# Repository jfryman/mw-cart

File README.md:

# mw-cart
MegaWiFi Cartridge

> **This is the MegaWiFi Rev.C fork** of [doragasu/mw-cart](https://gitlab.com/doragasu/mw-cart).
> Everything below the "Rev.C" section is doragasu's original README.

## Rev.C (this fork)

**What changed (2026-10-06, jfryman):** the NXP **SC16C550BIBS** UART (U7) is out of stock
everywhere, so Rev.C replaces it with the pin-compatible **TI TL16C550DRHB** (VQFN-32, RHB):

| | Rev.B (upstream) | Rev.C |
|---|---|---|
| U7 UART | NXP SC16C550BIBS | TI TL16C550DRHB (LCSC C2653239) |
| Y1 crystal | 24 MHz | **20 MHz** (C252261) + R18 1 MΩ bias resistor |
| Cart ↔ ESP32 link | 1.5 Mbaud | **1.25 Mbaud** |
| RI pin | NC | tied to VCC |

The TI part is rated to 20 MHz at 3.3 V, so the UART link runs at 1.25 Mbaud. **Rev.C is not
compatible with existing MegaWiFi ROMs or firmware**: ROMs need `UART_CLK` 20 MHz in their
`16c550.h`, and the ESP32 needs the Rev.C firmware from
[jfryman/mw-fw-rtos](https://github.com/jfryman/mw-fw-rtos/releases). Title blocks and silkscreen
are marked Rev.C.

**Status:** 10 boards assembled by JLCPCB (2026-10). The first board passes the full bring-up
suite at 1.25 Mbaud, including the flat 8 MiB ROM map with a Mega-CD and 32X attached.

**In this repo, beyond upstream:**
- `bringup-rom/`: a standalone 68000 test ROM for new boards (UART, crystal, ESP32 link,
  flash address lines, the 8 MiB map), plus a MAME simulation and FlashKit MD helper scripts.
- `tools/`: kicad-cli build wrapper and the KiCad s-expression helpers used for the U7 swap.
  `tools/fetch-ext.sh` fetches the Espressif 3D models.
- `lode/`: design notes, decisions and bench results.

**Downloads** ([releases](https://github.com/jfryman/mw-cart/releases)): JLCPCB Gerber zip,
BOM and CPL, schematic and fab PDFs, and the bring-up ROM. Upstream's own Rev.B outputs are on
[GitLab](https://gitlab.com/doragasu/mw-cart). Their BOM lists the unobtainable SC16C550BIBS.

---

This is the cartridge for the MegaWiFi project. It consists of a cartridge for the SEGA Genesis/Megadrive console, along with a WiFi interface, allowing brave programmers to implement games with online gaming, leaderboards, evil DLCs, etc.

This project was initially created for 1985alternativo, and to this day, as far as I know, only 1985 WorldCup game has used it to implement online play. Will you give it a try?

Have a look to the [github project page](https://gitlab.com/doragasu/mw) for more information.

## Cartridge specs

The current cartridge is based on an ESP32-C3 WiFi microcontroller, that has a good specs/price tradeoff. But bear in mind that if needed, it would be easy swapping it for other more powerful ESP32 chip, like for example the ESP32-S3. The current specs are:

* Up to 64 megabits (8 MiB) of flat ROM (no mapper needed!).
* Fast ESP32 to m68k UART bridge (1.5 Mbps baud rate with hardware flow control; 1.25 Mbps on Rev.C).
* 32-bit RISC-V CPU running at 160 MHz. Can be upgraded to dual core up to 240 MHz if needed.
* Additional 16 megabits (2 MiB) available of readable/writable memory (managed by the ESP32 and accessed through the UART bridge, could be upgraded to up to 14 MiB if needed!).
* 400 KiB of SRAM managed by the ESP32.
* 802.11bgn Wi-Fi (2.4 GHz band) with WPA3 support.
* Bluetooth Low Energy (BLE) support.
* USB port for ESP32 programming and debugging. Can be upgraded to work as general purpose USB host/device port.
* Connection to the cart audio input, so the chip could be used to produce additional sound (though there is no software support for this yet).

**Note**: The cartridge slashes the the usual 32 megabits maximum of ROM space by implementing a hack: it unmaps the MegaCD and uses its address space. This has the drawback that you cannot access the MegaCD when the hack is enabled. If you need to access the MegaCD, the hack can be disabled, but then the cart is limited to the usual 32 megabits of ROM.

## License
mw-cart is licensed under the [CERN OHL 1.2](http://www.ohwr.org/licenses/cern-ohl/v1.2) license. You are free to study, distribute and make modifications to the Documentation, under the aforementioned license terms.

## About CAD files
Electronic CAD design files are for KiCAD Open Source electronics design suite. Please install latest version along with KiCAD libraries to open the project. When opening schematic, KiCAD will most likely complain about missing library "doragasu". Despite this warning, the schematic should load nicely (using the cached libraries). To avoid this message, install [the missing library](https://github.com/doragasu/doragasu-kicad-lib) and make sure to configure it in the schematic editor.

## Board fabrication

You can go to [the package registry](https://gitlab.com/doragasu/mw-cart/-/packages) to download artifact packages with the fabrication files, including Gerbers, bill of materials, drawings, CPL file, etc. To get the PCB made, you sould have some knowledge about PCB manufacturing, but I will try to give some indications about how to get the boards made and assembled by JLCPCB.

### Manufacturing process example: JLCPCB

[JLCPCB](https://jlcpcb.com/) is a widely known Chinese PCB manufacturer, that can do PCB fabrication and assembly, including component procurement. They are fairly cheap for PCB prototypes and quality is pretty good for boards not having difficult components (such as BGAs with very fine pitch). One of the things that make them have quite competitive pricing, is that **they will only assemble components they have stocked**. Luckily they source components from [LCSC](https://www.lcsc.com/) (one of the biggest Chinese suppliers) and have a very wide catalog of components. But even with this wide catalog it is not uncommon that one or more of the components for your board are not available. In this case, they allow you to purchase the components through their platform, and once they receive them, they can be selected for assembly on your boards.

So roughly speaking, the procedure to order assembled PCBs on JLCPCB is as follows:

1. Get a quotation for PCB manufacturing and assembly.
2. If all components required for assembly are available, awesome, make the order and you have finished. Otherwise, purchase the components using their *Parts Manager*. Once purchased, stocked components usually take 2 or 3 weeks to be received by JLCPCB, and they will notify you via email.
3. Repeat step one, components you purchased through *Parts Manager* will be available for assembly on your boards.

Getting into the details, the procedure is:

1. Download the [PCB artifact package](https://gitlab.com/doragasu/mw-cart/-/packages) from the package registry.
2. Extract the package and locate the `Fab/Manufacturers/mega-wifi-JLCPCB.zip` file, that contains the Gerber files, the `Fab/Manufacturers/JLCPCB/mega-wifi_bom_jlc.csv` that has the BoM (Bill of Materials) and the `Fab/Manufacturers/JLCPCB/mega-wifi_cpl_jlc.csv` that has the CPL (Component Placement/Centroid) file. We will have to upload these files later.
3. Go to [JLCPCB](https://jlcpcb.com/) and log into your account. Then click *Order now* on the top right of the page.
4. Click *Add gerber file* and upload the `mega-wifi-JLCPCB.zip` file we located in step 2. When the files are processed, many board parameters will be populated. Most of the default values will be OK, but some changes are recommended. I will mark with an asterisk (\*) the parameters that should be changed from defaults, and will omit some parameters that should be clear enough (like PCB quantity, color, or dimensions that will be automatically obtained from Gerber files):

* Base material: FR-4
* Layers: 2
* PCB Thickness: 1.6
* Surface Finish: ENIG (\*)
* Outer Copper Weight: 1 oz
* Via Covering: Tented
* Min via hole size/diameter: 0.3mm
* Board Outline Tolerance: +- 0.2mm(Regular)
* Gold Fingers: Yes (\*)
* 30°finger chamfered: Yes (\*)
* Castellated Holes: No
* Edge Plating: No

5. If you want assembly, enable the *PCB Assembly* slider. All the default assembly parameters should be OK:

* PCBA Type: Standard
* Assembly Side: Top Side
* Edge Rails/Fiducials: Added by JLCPCB
* Parts Selection: By Customer

Advanced options defaults should also be OK.

6. Click "Next", you will be asked for confirmation about the side that will be assembled and the assembly quantity. Again, click "Next". Then you will be prompted for the BOM and CPL files. Upload the `mega-wifi_bom_jlc.csv` and `mega-wifi_cpl_jlc.csv` files we located in step 2. Then click "Process BOM & CPL".
7. You will be presented the table of components that will be assembled. If you are lucky, everything will be stocked so you can click "Next" and jump to step 12. Otherwise take note of the non stocked components (and I would also recommend taking note of stocked components having low stock) and continue to step 8.
8. Open the "Parts Manager" and the "Order Parts" on the left column.
9. Search for the non stocked parts from step 7. I would recommend searching first on the "JLCPCB Parts" section (that is usually cheaper and faster), but most likely you will have to search in the "Global Sourcing Parts". I would recommend only purchasing components in stock, because orders with components having a Lead Time, in my experience sometimes get heavily delayed or even cancelled.
10. Complete the components order, and wait till they are received by JLCPCB (they will notify by email). For stocked components, this should take 2 or 3 weeks max.
11. Repeat steps 1 to 7. Now you should be able to select your purchased components for the assembly.
12. You will be presented a component placement preview. It is a common issue that all components have a wrong offset from the board origin, and some can be wrongly rotated. Do not worry, this is normal and will be later corrected by the DFM analysis. Just click "Next".
13. You can now review the order, place it to the cart and proceed to checkout. Done! Just have to wait for the boards to arrive to your door. Be warned though that depending on your country and the shipping method, you might have to fill additional paperwork and pay import customs.

Enjoy!

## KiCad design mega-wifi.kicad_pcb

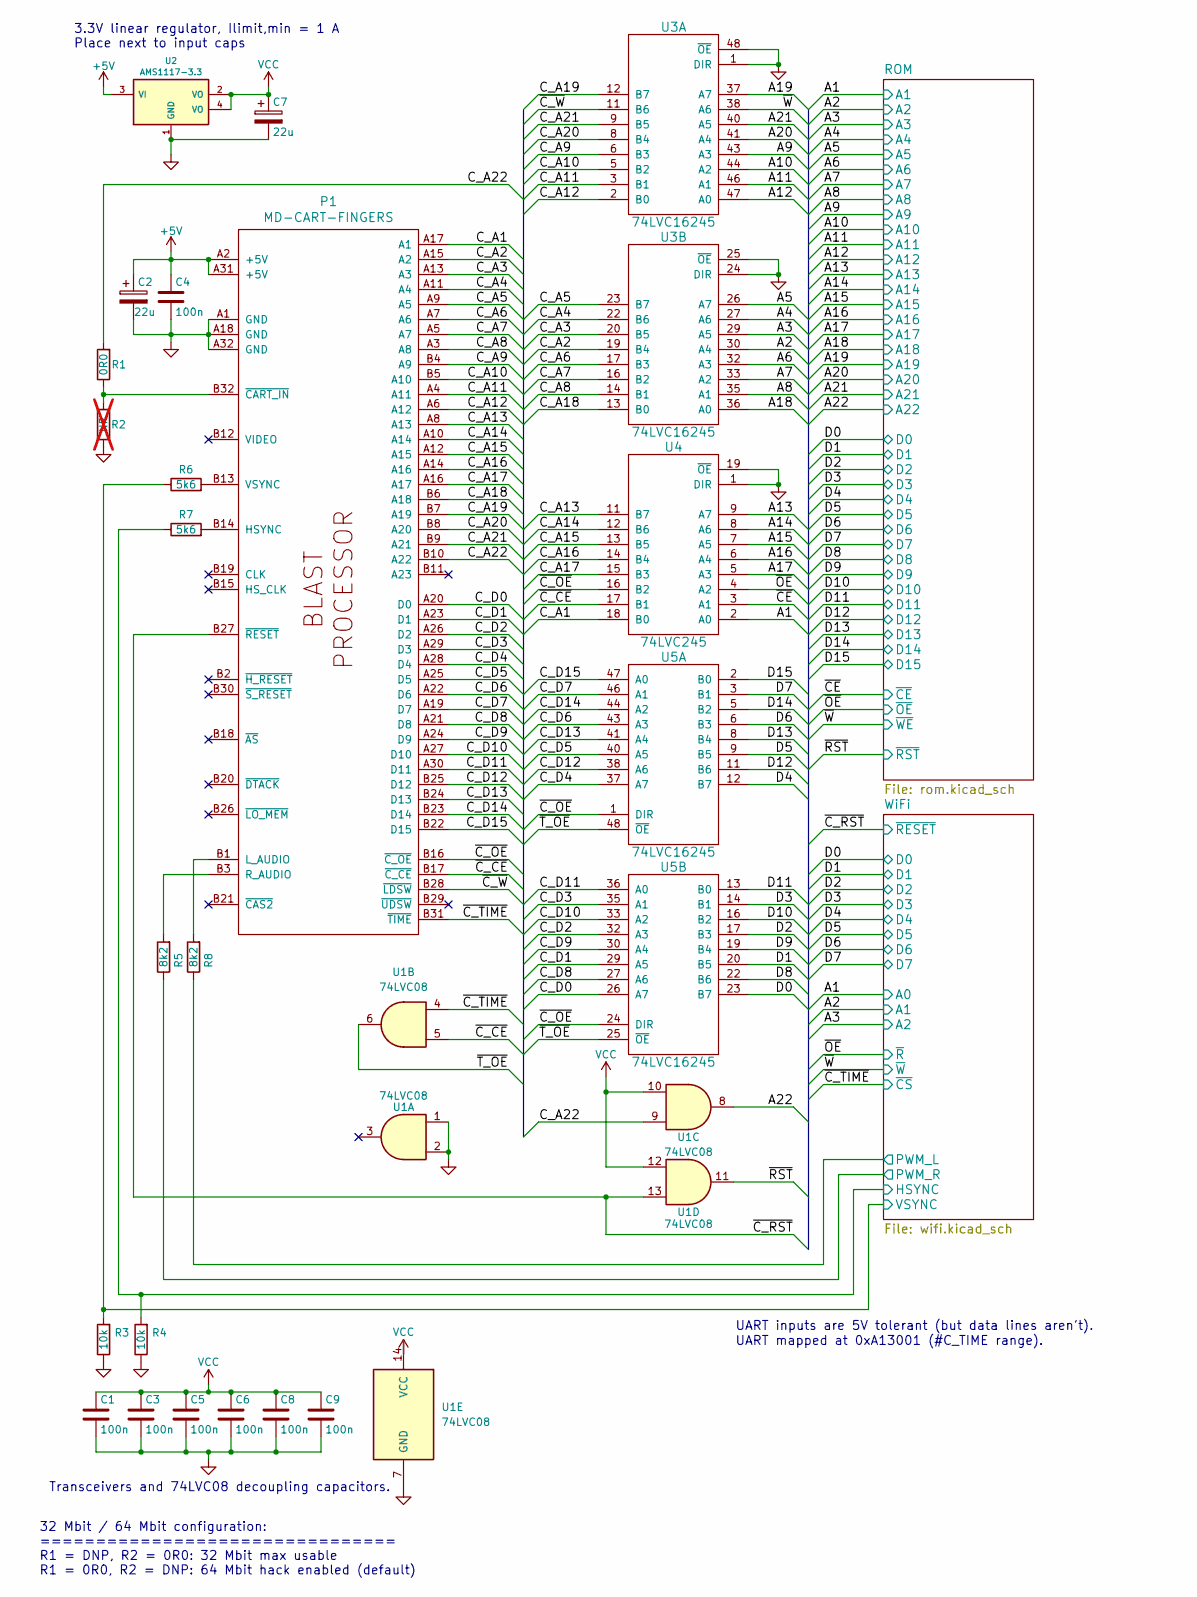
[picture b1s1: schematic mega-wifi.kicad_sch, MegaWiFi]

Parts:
C1, C3, C4, C5, C6, C8, C9: 100n; C_0603_1608Metric; LCSC# C14663
C2, C7: 22u; C_1206_3216Metric; LCSC# C12891
P1: MD-CART-FINGERS
R1: 0R0; R_0603_1608Metric; LCSC# C21189
R2: NP; R_0603_1608Metric; not fitted
R3, R4: 10k; R_0603_1608Metric; LCSC# C25804
R5, R8: 8k2; R_0603_1608Metric; LCSC# C25981
R6, R7: 5k6; R_0603_1608Metric; LCSC# C23189
U1: 74LVC08; TSSOP-14_4.4x5mm_P0.65mm; LCSC# C6053
U2: AMS1117-3.3; SOT-223; LCSC# C6186
U3, U5: 74LVC16245; TSSOP-48_6.1x12.5mm_P0.5mm; LCSC# C7824
U4: 74LVC245; TSSOP-20_4.4x6.5mm_P0.65mm; LCSC# C7848

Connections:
+5V: C2.1, C4.1, P1.A2 (+5V), P1.A31 (+5V), U2.3 (VI); also elsewhere on the board
/A1: U4.2 (A0); also elsewhere on the board
/A2: U3.30 (A4); also elsewhere on the board
/A3: U3.29 (A5); also elsewhere on the board
/A4: U3.27 (A6); also elsewhere on the board
/A5: U3.26 (A7); also elsewhere on the board
/A6: U3.32 (A3); also elsewhere on the board
/A7: U3.33 (A2); also elsewhere on the board
/A8: U3.35 (A1); also elsewhere on the board
/A9: U3.43 (A3); also elsewhere on the board
/A10: U3.44 (A2); also elsewhere on the board
/A11: U3.46 (A1); also elsewhere on the board
/A12: U3.47 (A0); also elsewhere on the board
/A13: U4.9 (A7); also elsewhere on the board
/A14: U4.8 (A6); also elsewhere on the board
/A15: U4.7 (A5); also elsewhere on the board
/A16: U4.6 (A4); also elsewhere on the board
/A17: U4.5 (A3); also elsewhere on the board
/A18: U3.36 (A0); also elsewhere on the board
/A19: U3.37 (A7); also elsewhere on the board
/A20: U3.41 (A4); also elsewhere on the board
/A21: U3.40 (A5); also elsewhere on the board
/A22: U1.8; also elsewhere on the board
/C_A1: P1.A17 (A1), U4.18 (B0)
/C_A2: P1.A15 (A2), U3.19 (B4)
/C_A3: P1.A13 (A3), U3.20 (B5)
/C_A4: P1.A11 (A4), U3.22 (B6)
/C_A5: P1.A9 (A5), U3.23 (B7)
/C_A6: P1.A7 (A6), U3.17 (B3)
/C_A7: P1.A5 (A7), U3.16 (B2)
/C_A8: P1.A3 (A8), U3.14 (B1)
/C_A9: P1.B4 (A9), U3.6 (B3)
/C_A10: P1.B5 (A10), U3.5 (B2)
/C_A11: P1.A4 (A11), U3.3 (B1)
/C_A12: P1.A6 (A12), U3.2 (B0)
/C_A13: P1.A8 (A13), U4.11 (B7)
/C_A14: P1.A10 (A14), U4.12 (B6)
/C_A15: P1.A12 (A15), U4.13 (B5)
/C_A16: P1.A14 (A16), U4.14 (B4)
/C_A17: P1.A16 (A17), U4.15 (B3)
/C_A18: P1.B6 (A18), U3.13 (B0)
/C_A19: P1.B7 (A19), U3.12 (B7)
/C_A20: P1.B8 (A20), U3.8 (B4)
/C_A21: P1.B9 (A21), U3.9 (B5)
/C_A22: P1.B10 (A22), R1.2, U1.9
/C_D0: P1.A20 (D0), U5.26 (A7)
/C_D1: P1.A23 (D1), U5.29 (A5)
/C_D2: P1.A26 (D2), U5.32 (A3)
/C_D3: P1.A29 (D3), U5.35 (A1)
/C_D4: P1.A28 (D4), U5.37 (A7)
/C_D5: P1.A25 (D5), U5.40 (A5)
/C_D6: P1.A22 (D6), U5.43 (A3)
/C_D7: P1.A19 (D7), U5.46 (A1)
/C_D8: P1.A21 (D8), U5.27 (A6)
/C_D9: P1.A24 (D9), U5.30 (A4)
/C_D10: P1.A27 (D10), U5.33 (A2)
/C_D11: P1.A30 (D11), U5.36 (A0)
/C_D12: P1.B25 (D12), U5.38 (A6)
/C_D13: P1.B24 (D13), U5.41 (A4)
/C_D14: P1.B23 (D14), U5.44 (A2)
/C_D15: P1.B22 (D15), U5.47 (A0)
/D0: U5.23 (B7); also elsewhere on the board
/D1: U5.20 (B5); also elsewhere on the board
/D2: U5.17 (B3); also elsewhere on the board
/D3: U5.14 (B1); also elsewhere on the board
/D4: U5.12 (B7); also elsewhere on the board
/D5: U5.9 (B5); also elsewhere on the board
/D6: U5.6 (B3); also elsewhere on the board
/D7: U5.3 (B1); also elsewhere on the board
/D8: U5.22 (B6); also elsewhere on the board
/D9: U5.19 (B4); also elsewhere on the board
/D10: U5.16 (B2); also elsewhere on the board
/D11: U5.13 (B0); also elsewhere on the board
/D12: U5.11 (B6); also elsewhere on the board
/D13: U5.8 (B4); also elsewhere on the board
/D14: U5.5 (B2); also elsewhere on the board
/D15: U5.2 (B0); also elsewhere on the board
/WiFi/HSYNC: R4.2, R7.1; also elsewhere on the board
/WiFi/PWM_L: R8.1; also elsewhere on the board
/WiFi/PWM_R: R5.1; also elsewhere on the board
/WiFi/VSYNC: R3.2, R6.1; also elsewhere on the board
/~CE: U4.3 (A1); also elsewhere on the board
/~C_CE: P1.B17 (~C_CE), U1.5, U4.17 (B1)
/~C_OE: P1.B16 (~C_OE), U4.16 (B2), U5.1 (DIR), U5.24 (DIR)
/~C_RST: P1.B27 (~RESET), U1.13; also elsewhere on the board
/~C_TIME: P1.B31 (~TIME), U1.4; also elsewhere on the board
/~C_W: P1.B28 (~LDSW), U3.11 (B6)
/~OE: U4.4 (A2); also elsewhere on the board
/~RST: U1.11; also elsewhere on the board
/~T_OE: U1.6, U5.25 (~OE), U5.48 (~OE)
/~W: U3.38 (A6); also elsewhere on the board
GND: C1.2, C2.2, C3.2, C4.2, C5.2, C6.2, C7.2, C8.2, C9.2, P1.A1 (GND), P1.A18 (GND), P1.A32 (GND), R2.1, R3.1, R4.1, U1.1, U1.2, U1.7 (GND), U2.1 (GND), U3.1 (DIR), U3.4 (GND), U3.10 (GND), U3.15 (GND), U3.21 (GND), U3.24 (DIR), U3.25 (~OE), U3.28 (GND), U3.34 (GND), U3.39 (GND), U3.45 (GND), U3.48 (~OE), U4.1 (DIR), U4.10 (GND), U4.19 (~OE), U5.4 (GND), U5.10 (GND), U5.15 (GND), U5.21 (GND), U5.28 (GND), U5.34 (GND), U5.39 (GND), U5.45 (GND); also elsewhere on the board
unnamed: P1.B14 (HSYNC), R7.2
unnamed: P1.B1 (L_AUDIO), R8.2
unnamed: P1.B3 (R_AUDIO), R5.2
unnamed: P1.B13 (VSYNC), R6.2
unnamed: P1.B32 (~CART_IN), R1.1, R2.2
VCC: C1.1, C3.1, C5.1, C6.1, C7.1, C8.1, C9.1, U1.10, U1.12, U1.14 (VCC), U2.2 (VO), U2.4 (VO), U3.7 (VCC), U3.18 (VCC), U3.31 (VCC), U3.42 (VCC), U4.20 (VCC), U5.7 (VCC), U5.18 (VCC), U5.31 (VCC), U5.42 (VCC); also elsewhere on the board

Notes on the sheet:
UART mapped at 0xA13001 (#C_TIME range).
32 Mbit / 64 Mbit configuration: ================================ R1 = DNP, R2 = 0R0: 32 Mbit max usable R1 = 0R0, R2 = DNP: 64 Mbit hack enabled (default)
Transceivers and 74LVC08 decoupling capacitors.
UART inputs are 5V tolerant (but data lines aren't).
3.3V linear regulator, Ilimit,min = 1 A Place next to input caps

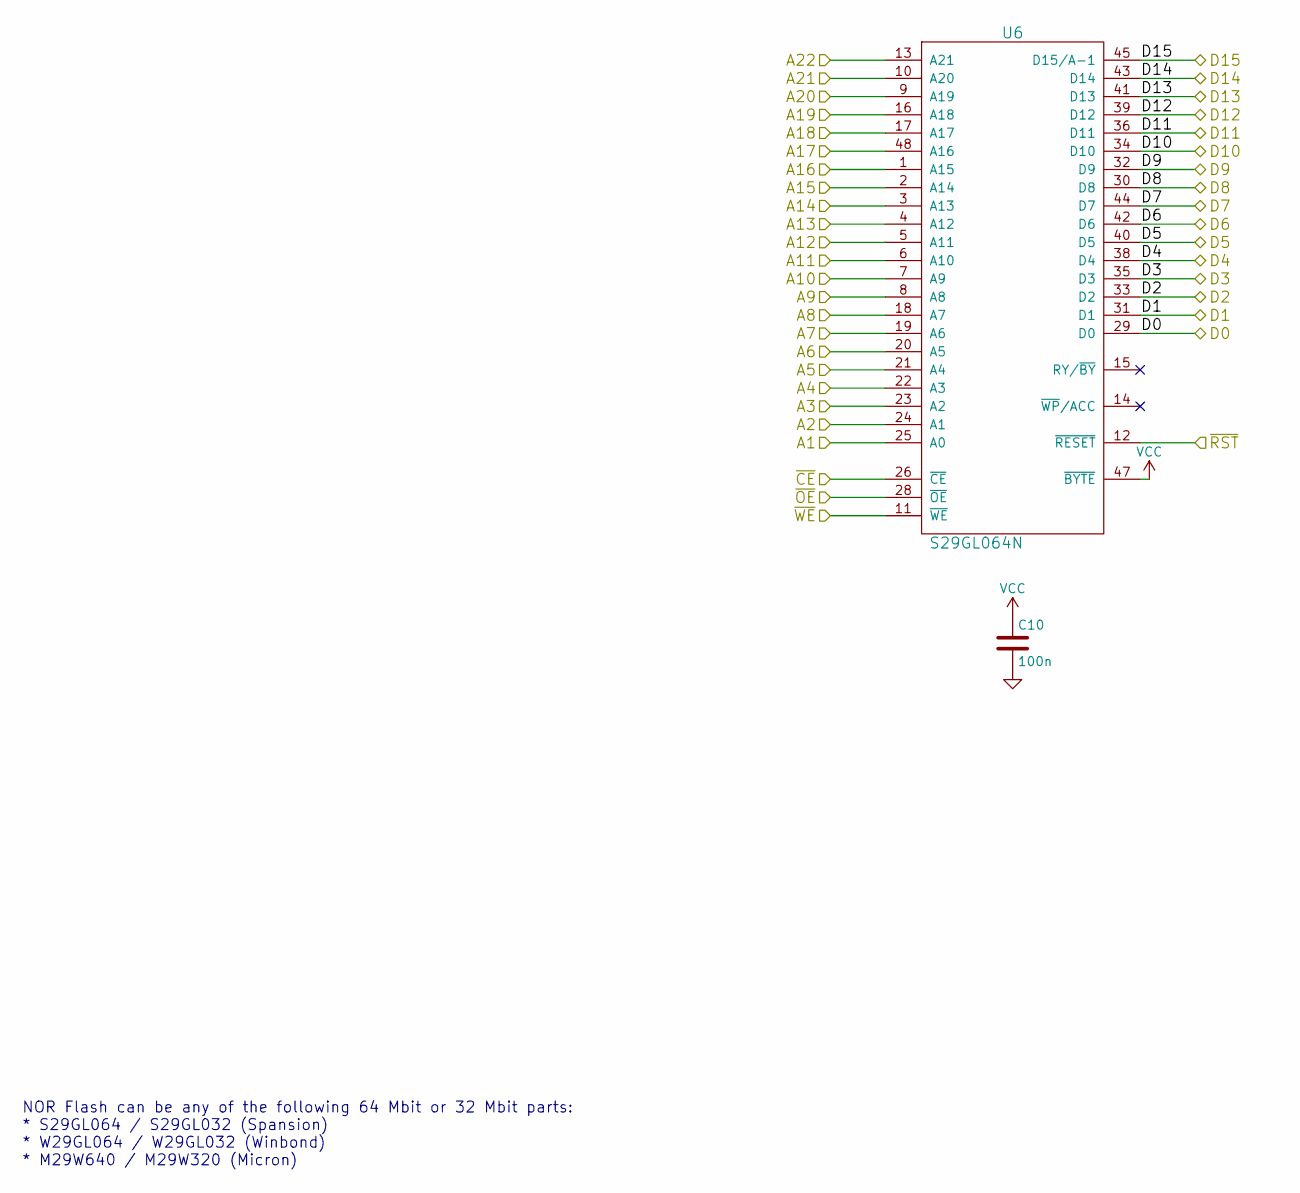
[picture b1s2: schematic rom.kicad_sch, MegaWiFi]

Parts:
C10: 100n; C_0603_1608Metric; LCSC# C14663
U6: S29GL064N; TSOP-I-48_18.4x12mm_P0.5mm; LCSC# C117907

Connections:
/A1: U6.25 (A0); also elsewhere on the board
/A2: U6.24 (A1); also elsewhere on the board
/A3: U6.23 (A2); also elsewhere on the board
/A4: U6.22 (A3); also elsewhere on the board
/A5: U6.21 (A4); also elsewhere on the board
/A6: U6.20 (A5); also elsewhere on the board
/A7: U6.19 (A6); also elsewhere on the board
/A8: U6.18 (A7); also elsewhere on the board
/A9: U6.8 (A8); also elsewhere on the board
/A10: U6.7 (A9); also elsewhere on the board
/A11: U6.6 (A10); also elsewhere on the board
/A12: U6.5 (A11); also elsewhere on the board
/A13: U6.4 (A12); also elsewhere on the board
/A14: U6.3 (A13); also elsewhere on the board
/A15: U6.2 (A14); also elsewhere on the board
/A16: U6.1 (A15); also elsewhere on the board
/A17: U6.48 (A16); also elsewhere on the board
/A18: U6.17 (A17); also elsewhere on the board
/A19: U6.16 (A18); also elsewhere on the board
/A20: U6.9 (A19); also elsewhere on the board
/A21: U6.10 (A20); also elsewhere on the board
/A22: U6.13 (A21); also elsewhere on the board
/D0: U6.29 (D0); also elsewhere on the board
/D1: U6.31 (D1); also elsewhere on the board
/D2: U6.33 (D2); also elsewhere on the board
/D3: U6.35 (D3); also elsewhere on the board
/D4: U6.38 (D4); also elsewhere on the board
/D5: U6.40 (D5); also elsewhere on the board
/D6: U6.42 (D6); also elsewhere on the board
/D7: U6.44 (D7); also elsewhere on the board
/D8: U6.30 (D8); also elsewhere on the board
/D9: U6.32 (D9); also elsewhere on the board
/D10: U6.34 (D10); also elsewhere on the board
/D11: U6.36 (D11); also elsewhere on the board
/D12: U6.39 (D12); also elsewhere on the board
/D13: U6.41 (D13); also elsewhere on the board
/D14: U6.43 (D14); also elsewhere on the board
/D15: U6.45 (D15/A-1); also elsewhere on the board
/~CE: U6.26 (~CE); also elsewhere on the board
/~OE: U6.28 (~OE); also elsewhere on the board
/~RST: U6.12 (~RESET); also elsewhere on the board
/~W: U6.11 (~WE); also elsewhere on the board
GND: C10.2, U6.27 (GND), U6.46 (GND); also elsewhere on the board
VCC: C10.1, U6.37 (VCC), U6.47 (~BYTE); also elsewhere on the board

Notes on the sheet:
NOR Flash can be any of the following 64 Mbit or 32 Mbit parts: * S29GL064 / S29GL032 (Spansion) * W29GL064 / W29GL032 (Winbond) * M29W640 / M29W320 (Micron)

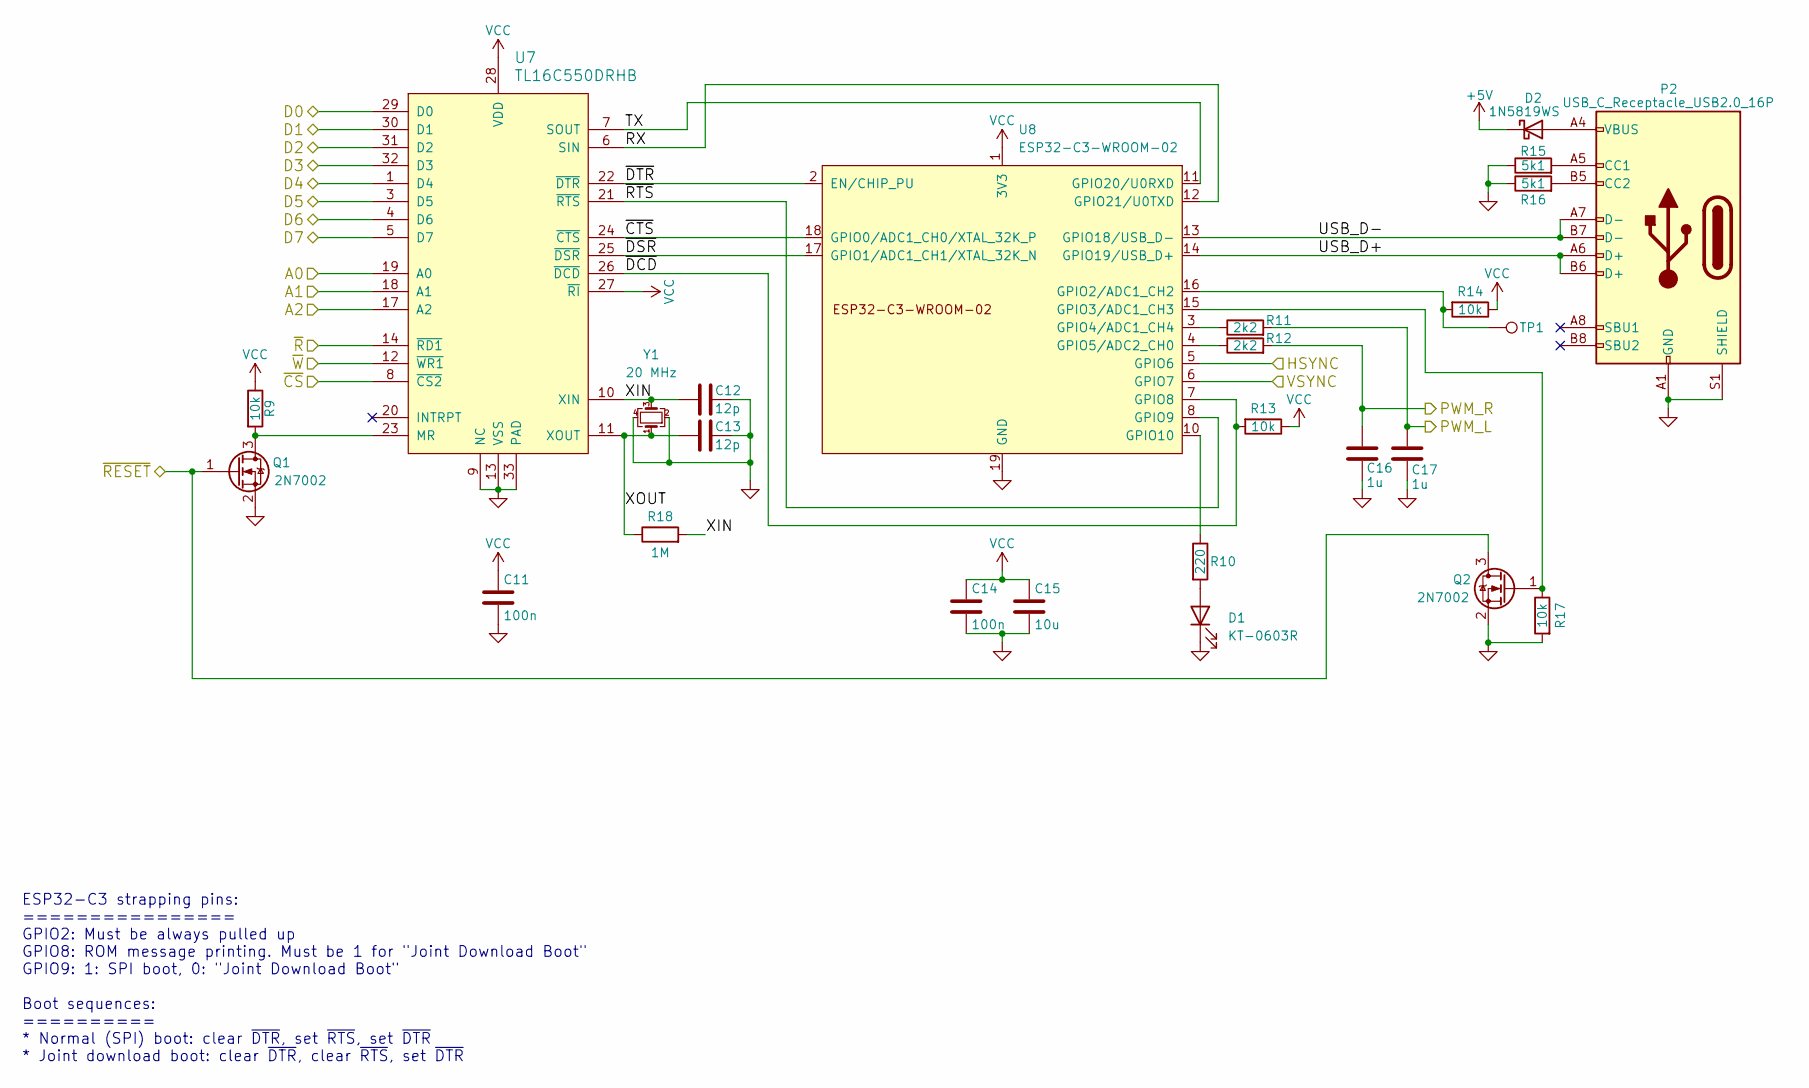
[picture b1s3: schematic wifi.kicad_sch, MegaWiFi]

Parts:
C11, C14: 100n; C_0603_1608Metric; LCSC# C14663
C12, C13: 12p; C_0603_1608Metric; LCSC# C38523
C15: 10u; C_0805_2012Metric; LCSC# C15850
C16, C17: 1u; C_0805_2012Metric; LCSC# C28323
D1: KT-0603R; LED_0603_1608Metric; LCSC# C2286
D2: 1N5819WS; D_SOD-323; LCSC# C191023
P2: USB_C_Receptacle_USB2.0_16P; USB_C_Receptacle_HCTL_HC-TYPE-C-16P-01A; LCSC# C709357
Q1, Q2: 2N7002; SOT-23; LCSC# C8545
R9, R13, R14, R17: 10k; R_0603_1608Metric; LCSC# C25804
R10: 220; R_0603_1608Metric; LCSC# C22962
R11, R12: 2k2; R_0603_1608Metric; LCSC# C4177
R15, R16: 5k1; R_0402_1005Metric; LCSC# C25905
R18: 1M; R_0402_1005Metric; LCSC# C26083
TP1: TestPoint; TestPoint_Pad_D1.0mm
U7: TL16C550DRHB; Texas_RHB0032E_VQFN-32-1EP_5x5mm_P0.5mm_EP3.45x3.45mm; LCSC# C2653239
U8: ESP32-C3-WROOM-02; LCSC# C2934560
Y1: 20 MHz; Crystal_SMD_2520-4Pin_2.5x2.0mm; LCSC# C252261

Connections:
+5V: D2.1 (K); also elsewhere on the board
/A1: U7.19 (A0); also elsewhere on the board
/A2: U7.18 (A1); also elsewhere on the board
/A3: U7.17 (A2); also elsewhere on the board
/D0: U7.29 (D0); also elsewhere on the board
/D1: U7.30 (D1); also elsewhere on the board
/D2: U7.31 (D2); also elsewhere on the board
/D3: U7.32 (D3); also elsewhere on the board
/D4: U7.1 (D4); also elsewhere on the board
/D5: U7.3 (D5); also elsewhere on the board
/D6: U7.4 (D6); also elsewhere on the board
/D7: U7.5 (D7); also elsewhere on the board
/WiFi/HSYNC: U8.5 (GPIO6); also elsewhere on the board
/WiFi/PWM_L: C17.1, R11.2; also elsewhere on the board
/WiFi/PWM_R: C16.1, R12.2; also elsewhere on the board
/WiFi/RX: U7.6 (SIN), U8.12 (GPIO21/U0TXD)
/WiFi/TX: U7.7 (SOUT), U8.11 (GPIO20/U0RXD)
/WiFi/USB_D+: P2.A6 (D+), P2.B6 (D+), U8.14 (GPIO19/USB_D+)
/WiFi/USB_D-: P2.A7 (D-), P2.B7 (D-), U8.13 (GPIO18/USB_D-)
/WiFi/VSYNC: U8.6 (GPIO7); also elsewhere on the board
/WiFi/XIN: C12.2, R18.2, U7.10 (XIN), Y1.3
/WiFi/XOUT: C13.2, R18.1, U7.11 (XOUT), Y1.1
/WiFi/~CTS: U7.24 (~CTS), U8.18 (GPIO0/ADC1_CH0/XTAL_32K_P)
/WiFi/~DCD: R13.2, U7.26 (~DCD), U8.7 (GPIO8)
/WiFi/~DSR: U7.25 (~DSR), U8.17 (GPIO1/ADC1_CH1/XTAL_32K_N)
/WiFi/~DTR: U7.22 (~DTR), U8.2 (EN/CHIP_PU)
/WiFi/~RTS: U7.21 (~RTS), U8.8 (GPIO9)
/~C_RST: Q1.1 (G), Q2.3 (D); also elsewhere on the board
/~C_TIME: U7.8 (~CS2); also elsewhere on the board
/~OE: U7.14 (~RD1); also elsewhere on the board
/~W: U7.12 (~WR1); also elsewhere on the board
GND: C11.2, C12.1, C13.1, C14.2, C15.2, C16.2, C17.2, D1.1 (K), P2.A1 (GND), P2.A12 (GND), P2.B1 (GND), P2.B12 (GND), P2.S1 (SHIELD), Q1.2 (S), Q2.2 (S), R15.1, R16.1, R17.2, U7.9 (NC), U7.13 (VSS), U7.33 (PAD), U8.9 (GND), U8.19 (GND), Y1.2, Y1.4; also elsewhere on the board
unnamed: D1.2 (A), R10.2
unnamed: D2.2 (A), P2.A4 (VBUS), P2.A9 (VBUS), P2.B4 (VBUS), P2.B9 (VBUS)
unnamed: P2.A5 (CC1), R15.2
unnamed: P2.B5 (CC2), R16.2
unnamed: Q1.3 (D), R9.2, U7.23 (MR)
unnamed: Q2.1 (G), R17.1, U8.15 (GPIO3/ADC1_CH3)
unnamed: R14.2, TP1.1, U8.16 (GPIO2/ADC1_CH2)
unnamed: R11.1, U8.3 (GPIO4/ADC1_CH4)
unnamed: R12.1, U8.4 (GPIO5/ADC2_CH0)
unnamed: R10.1, U8.10 (GPIO10)
VCC: C11.1, C14.1, C15.1, R9.1, R13.1, R14.1, U7.27 (~RI), U7.28 (VDD), U8.1 (3V3); also elsewhere on the board

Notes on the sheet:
ESP32-C3 strapping pins: ================ GPIO2: Must be always pulled up GPIO8: ROM message printing. Must be 1 for "Joint Download Boot" GPIO9: 1: SPI boot, 0: "Joint Download Boot" Boot sequences: ========== * Normal (SPI) boot: clear ~{DTR}, set ~{RTS}, set ~{DTR} * Joint download boot: clear ~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

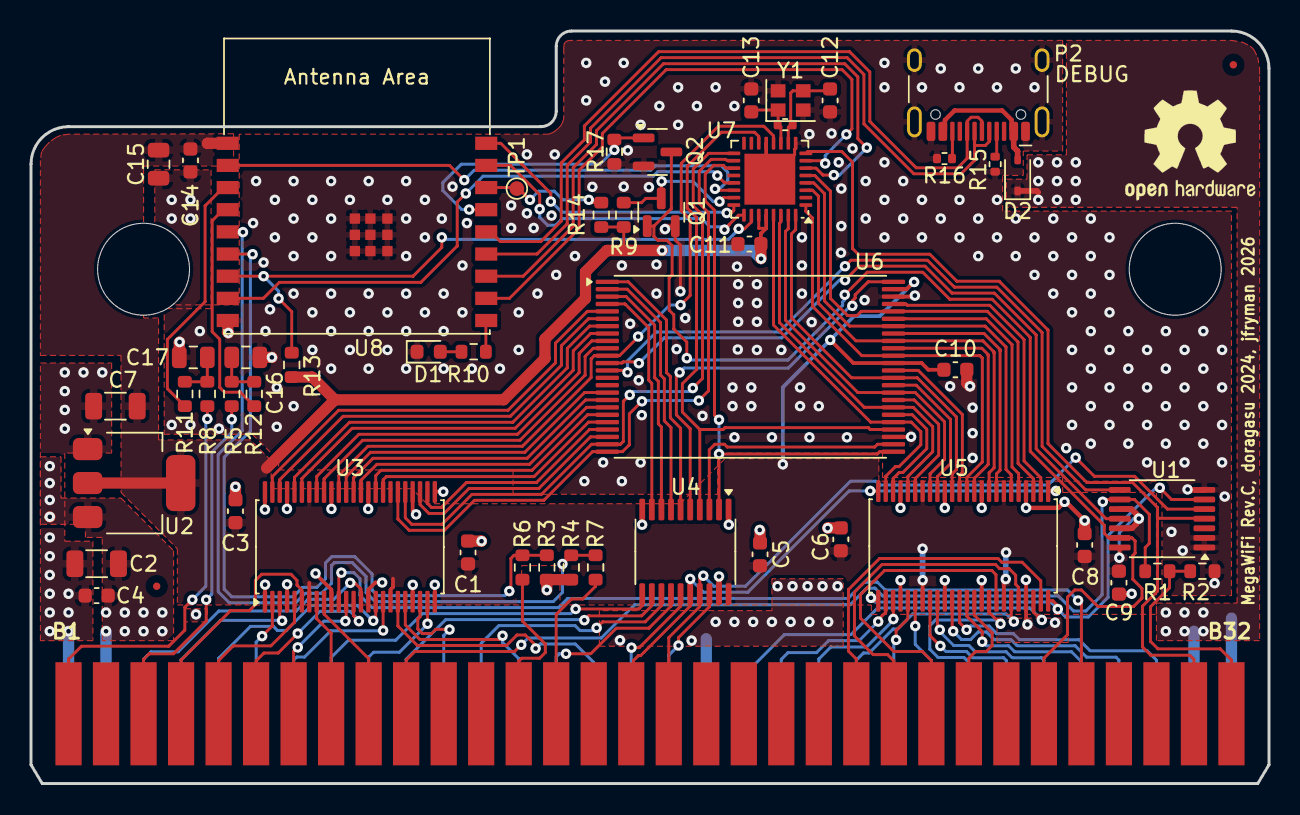
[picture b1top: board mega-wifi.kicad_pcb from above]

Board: 2 copper layers, 83.8 x 51.0 mm, 51 parts (0 on the bottom side), 119 nets.

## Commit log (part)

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2022-01-08 Change github reference to gitlab
2023-04-23 Update to KiCad 7
2023-04-23 Add CI/CD Kibot integration
2023-04-23 Minor tweaks
2024-09-29 Update schematics for Rev.B:
    * Switch obsolete SC16C554BIB48 with SC16C554BIBS
    * Change ESP8266 with ESP32-C3
    * Add USB-C connector for flashing/debugging
2024-10-07 Rev.B PCB
    * Replace obsolete SC16C550BIB48 with SC16C550BIBS
    * Replace ESP8266 with ESP32-C3
    * Implement 64 Mbit hack
    * Add USB-C debug header for ESP32-C3
    * Many PCB improvements
2024-10-07 Use KiCAD 8 KiBot image
2024-10-08 Fabrication tweaks
2024-10-09 Allow ESP32 to reset the host
2024-12-04 Update README.md with PCB fabrication instructions for JLCPCB
2024-12-07 Replace photograph with new cart
2025-02-24 README: Add rough cart specs

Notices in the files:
mega-wifi.kicad_pcb:
License: CERN OHL 1.2
